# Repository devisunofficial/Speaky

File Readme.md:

# Speaky

Speaky is a bluetooth speaker that uses ESP32 for bluetooth connection

It focuses on minimalism and uses Audiophile grade equipments for good soundquality

### Features:

 - Compact design 
 - Capacitive Sensor to enter pairing mode
 - Toggle switch to On-Off speaker.
 - Daytone Speaker and Passive Radiator

### CAD Model:
It has 3 separate printed pieces. The Enclosure, the Speaker Holder to support driver, and Top mesh to cover driver.
Made in Autodesk Fusion.

### PCB:
Here's my PCB! It was made in KiCad. 

Schematic : 
PCB Footprint : 

### Firmware Overview:
Currently Firmware is underdevelopment so there is some time to finished product.
This speaker uses C++ firmware and Arduino IDE for Flashing.

### Assembly Instructions :
1. Flash Firmware in XIAO ESO32
2. Solder Pairing Switch, Kill Switch, Speaker, Battery
3. Test everything works
4. Apply Epoxy layer(not neccessary though but better if we do) inside shell to prevent air from leaking
5. Glue togetther the Speaker and Passive Radiater to Speaker holder (to prevent air from leaking) along with screws
6. Screw Speaker holder and Top Mesh to Enclosure.

### BOM Table
|Name|Use|Quantity|Link|Distributer|
|----|---|--------|----|-----------|
|Passive Radiator| For Depth| 1|[Link](https://www.daytonaudio.com/product/1552/nd65-pr-2-1-2-aluminum-cone-passive-radiator)|Dayton Audio|
|Speaker|Main Driver|1|[Link](https://www.amazon.in/Dayton-Audio-DMA45-4-Aluminum-Full-Range/dp/B07N1YW3SV?crid=3V7R0WFBODGVD&dib=eyJ2IjoiMSJ9.ZovJ2FRQs3pmwyzB_tD3JRq4LaJKzlhPqWikw9393H10BYXCIcvu9hzi35ROTbgVzwRGON-UKmSIxJZb096X-t3fNUy7ZwafTm0j-v9W8j7VAd_8-LCThV547bfVhP9NJ7Wi9YgXWHFZLfnOVMGbUS30ZCycVPFoQHI8esF8xiJo9Ei9W604bymV5dHSm5gL.1QMB5W2LyaJ6eF8SeeBaS8edQjG50gg-gWsAIbsoJMA&dib_tag=se&keywords=dayton+audio+dma45-4&nsdOptOutParam=true&qid=1783793906&sbo=RZvfv%2F%2FHxDF%2BO5021pAnSA%3D%3D&sprefix=dayton+Audio+DMA%2Caps%2C292&sr=8-1)|Amazon|
|PCB|Main-Circuit|1|-|JLCPCB|
|Battery|Power Source|1|[Link](https://robu.in/product/nova-125785-10000mah-3-7v-lipo-battery-pack/)|Robu|
|Toggle switch|On-Off|1|[Link](https://www.amazon.in/RoboComp-Center-Rocker-Toggle-Switch/dp/B0GW1SK6Y5?dib=eyJ2IjoiMSJ9.1CwHqbAUYwizY1Z1K0WZdKre8CLLDpprYbmEb_9PNTWqyjohjF5RvFQHYgcRSr029HxOQ9XFU9Yd2WoFSByQLTZC4mpo1z00oP6VspIr7XqntChIDTYswrf3dJoaJTSpmRr7esG0u7r-XJnCxbD7MD168vrldx863bm8NWvZ2WL-OKQtGgTEFOjLlDHG3WGsgi2VIhzc2M38_9MY_n1VyhJtiu9AZsDnKbQQZl6pZYEsnpHDEuILOJHanJcoKXVOJf6PUo8NBcmJ2H5TxdEh0F4194ktdUkxSr8JhkX-HH0.AAfvh377-khgNbQY7kIIHbfBj4w8bifQznZzReEkcW0&dib_tag=se&qid=1781184118&refinements=p_n_g-1003565985111%3A61707331031&s=industrial&xpid=CJ1-0rXLg6M1t&th=1)|Amazon|

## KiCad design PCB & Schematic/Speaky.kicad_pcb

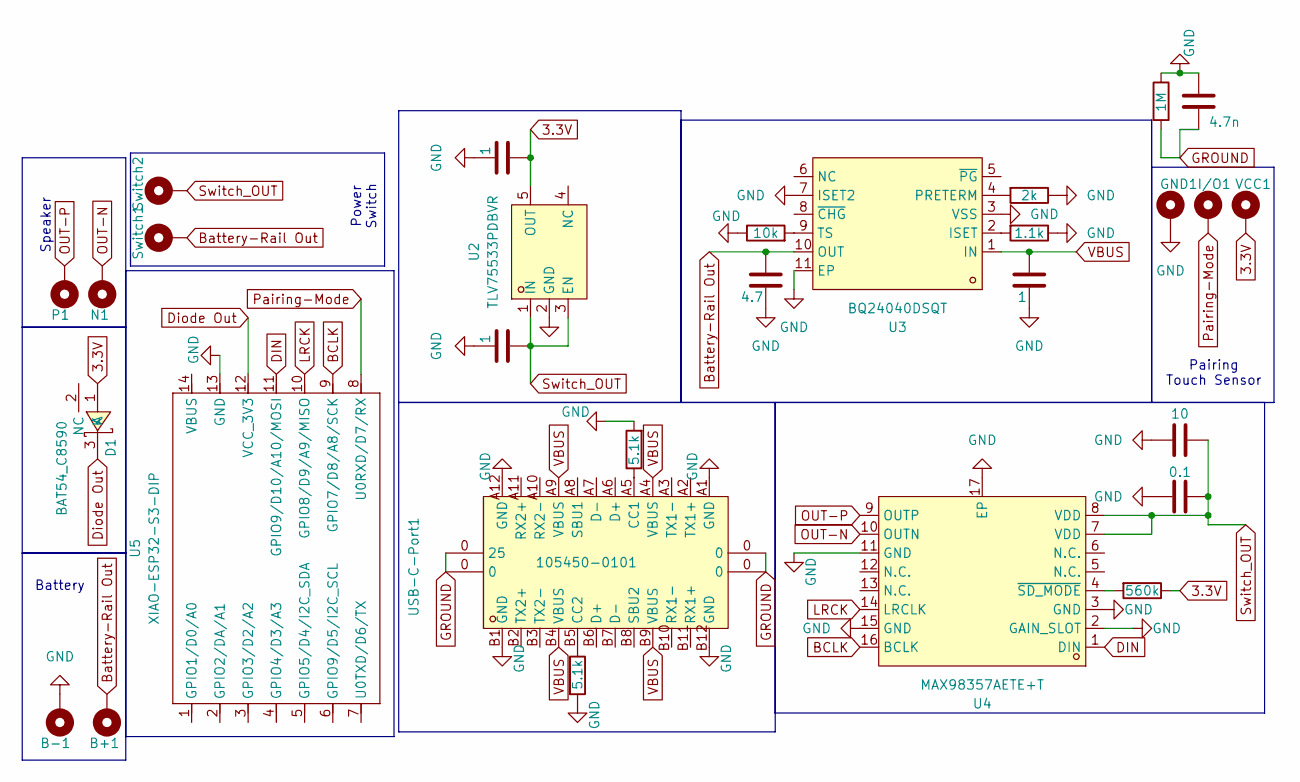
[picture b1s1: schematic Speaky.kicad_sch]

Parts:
B+1: MountingHole_Pad; SolderWirePad_1x01_SMD_2x4mm
B-1: MountingHole_Pad; SolderWirePad_1x01_SMD_2x4mm
C1: 0.1; C_0805_2012Metric
C2: 10; C_1206_3216Metric
C3, C5, C6: 1; C_0805_2012Metric
C4: 4.7; C_1206_3216Metric
C7: 4.7n; C_0805_2012Metric
D1: BAT54_C8590; SOT-23-3; MPN BAT54; LCSC Part C8590
GND1: MountingHole_Pad; SolderWirePad_1x01_SMD_2x4mm
I/O1: MountingHole_Pad; SolderWirePad_1x01_SMD_2x4mm
N1: MountingHole_Pad; SolderWirePad_1x01_SMD_2x4mm
P1: MountingHole_Pad; SolderWirePad_1x01_SMD_2x4mm
R1: 560k; R_0805_2012Metric
R2: 1.1k; R_0805_2012Metric
R3: 2k; R_0805_2012Metric
R4: 10k; R_0805_2012Metric
R5, R6: 5.1k; R_0805_2012Metric
R7: 1M; R_0805_2012Metric
Switch1, Switch2: MountingHole_Pad; SolderWirePad_1x01_SMD_2x4mm
U2: TLV75533PDBVR; SOT-23-5; MPN TLV75533PDBVR; LCSC Part C404027
U3: BQ24040DSQT; WSON-10_L2.0-W2.0-P0.40-TL-EP; MPN BQ24040DSQT; LCSC Part C2876332
U4: MAX98357AETE+T; TQFN-16_L3.0-W3.0-P0.50-BL-EP1.5; MPN MAX98357AETE+T; LCSC Part C910544
U5: XIAO-ESP32-S3-DIP; XIAO-Generic-Thruhole-14P-2.54-21X17.8MM
USB-C-Port1: 105450-0101; USB-C-SMD_TYPE-C-USB-18; MPN 1054500101; LCSC Part C134092
VCC1: MountingHole_Pad; SolderWirePad_1x01_SMD_2x4mm

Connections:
3.3V: C6.2, D1.1 (A), R1.1, U2.5 (OUT), VCC1.1 (1_1)
BCLK: U4.16 (BCLK), U5.9 (GPIO7/D8/A8/SCK)
Battery-Rail Out: B+1.1 (1_1), C4.2, Switch1.1 (1_1), U3.10 (OUT)
DIN: U4.1 (DIN), U5.11 (GPIO9/D10/A10/MOSI)
Diode Out: D1.3 (K), U5.12 (VCC_3V3)
GND: B-1.1 (1_1), C1.2, C2.2, C3.1, C4.1, C5.1, C6.1, C7.1, GND1.1 (1_1), R2.1, R3.1, R4.1, R5.2, R6.2, R7.1, U2.2 (GND), U3.3 (VSS), U3.7 (ISET2), U3.11 (EP), U4.2 (GAIN_SLOT), U4.3 (GND), U4.11 (GND), U4.15 (GND), U4.17 (EP), U5.13 (GND), USB-C-Port1.A1 (GND), USB-C-Port1.A12 (GND), USB-C-Port1.B1 (GND), USB-C-Port1.B12 (GND)
GROUND: C7.2, R7.2, USB-C-Port1.0
LRCK: U4.14 (LRCLK), U5.10 (GPIO8/D9/A9/MISO)
unnamed: R2.2, U3.2 (ISET)
unnamed: R3.2, U3.4 (PRETERM)
unnamed: R4.2, U3.9 (TS)
unnamed: R1.2, U4.4 (~SD_MODE)
unnamed: R6.1, USB-C-Port1.A5 (CC1)
unnamed: R5.1, USB-C-Port1.B5 (CC2)
OUT-N: N1.1 (1_1), U4.10 (OUTN)
OUT-P: P1.1 (1_1), U4.9 (OUTP)
Pairing-Mode: I/O1.1 (1_1), U5.8 (U0RXD/D7/RX)
Switch_OUT: C1.1, C2.1, C5.2, Switch2.1 (1_1), U2.1 (IN), U2.3 (EN), U4.7 (VDD), U4.8 (VDD)
VBUS: C3.2, U3.1 (IN), USB-C-Port1.A4 (VBUS), USB-C-Port1.A9 (VBUS), USB-C-Port1.B4 (VBUS), USB-C-Port1.B9 (VBUS)

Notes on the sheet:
Battery
Pairing Touch Sensor
Power Switch
Speaker

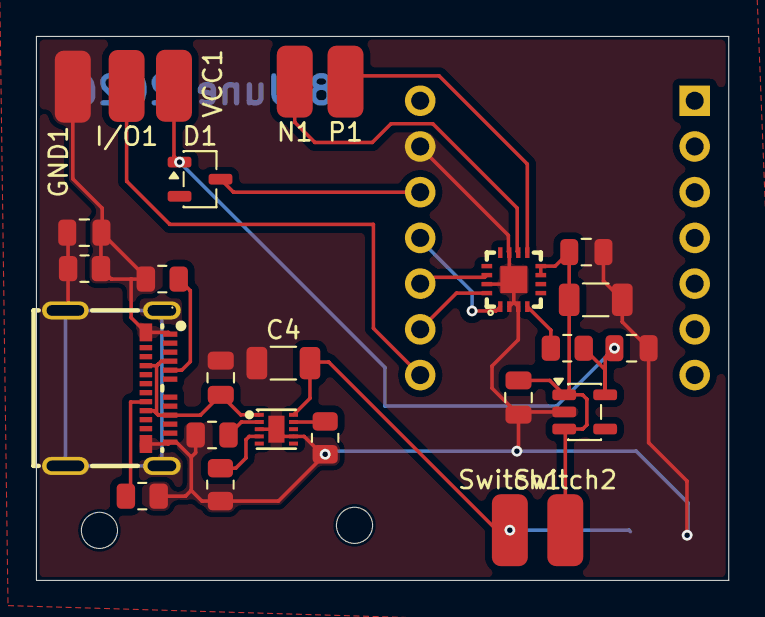
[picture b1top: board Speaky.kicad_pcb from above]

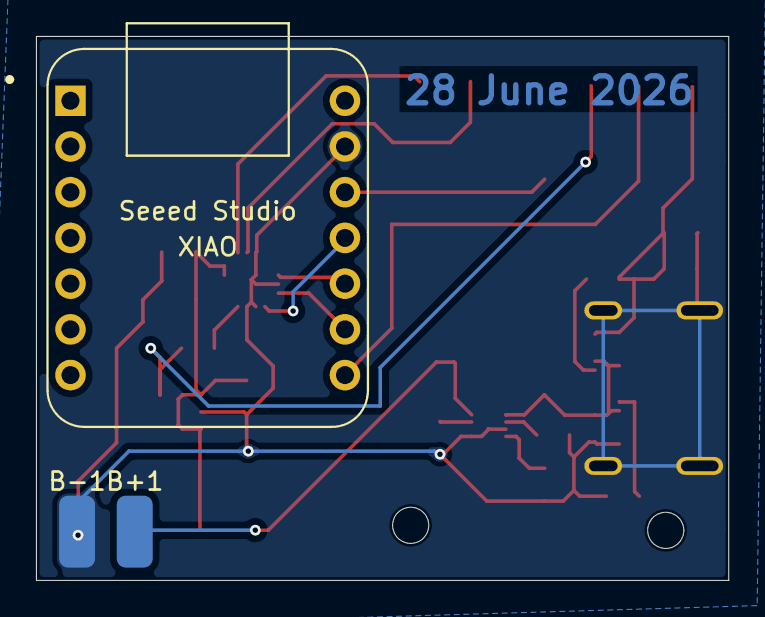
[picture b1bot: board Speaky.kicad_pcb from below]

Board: 2 copper layers, 38.5 x 30.2 mm, 29 parts (3 on the bottom side), 19 nets.

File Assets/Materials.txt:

1. Dayton Audio ND65-PR                                            (Passive Radiator)
2. Dayton Audio DMA45-4                                            (Full-Range Driver)
3. Polymaker PolyMax PETG or Prusament ABS                         (Filament To be used to make enclosure)
4. XFasten High-Density EVA Foam Tape + Loctite Clear Silicone     (Sealing & Damping)
5. Molex 105450-0101                                               (Mid- Mount USB C port)
6. MAX98357AETE+T                                                  (Class D Audio Amplifier)
7. BQ24040DSQT                                                     (Battery Charger IC)
8. Seeed Studio nRF52840                                           (Bluetooth SoC)
9. TLV75533PDBVR                                                   (Voltage Regulator (LDO))
10. BAT54                                                          (Schottky Diodes)

https://www.amazon.in/RoboComp-Center-Rocker-Toggle-Switch/d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
